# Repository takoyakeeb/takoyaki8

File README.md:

# takoyaki8

8キー(2行 × 4列)のマクロパッドです。マイコンは RP2040-Zero、ファームウェアは TinyGo(Go 言語)で書いています。
キーの割り当ては、Web ツール tinykeemap で書き換えられます。

## 特徴

- 8キー(2行 × 4列)。Choc v2 スイッチ(Choc v1 ではない)、ホットスワップ式(ソケット: CPG135001S30)
- マイコン: Waveshare RP2040-Zero
- 0.91 インチ OLED(128 × 32、I2C)と、フルカラー LED(WS2812B-V5)4個。OLED に、いまのレイヤーの番号と短い名前が出る
- ケース: トッププレート(メイン基板と同じパネルで製造)と、透明アクリル 2mm のボトムプレート・OLED カバー
- 4レイヤー。レイヤー切り替え(MO / TG / TO)と、Shift などの修飾キー付きのキーに対応
- キーマップは本体の Flash に保存できる(書き換えは tinykeemap)

## 部品リスト

### 基板に載せる部品

| 部品 | 型番・仕様 | 数量(1台) | 備考 |
|---|---|---|---|
| コンデンサ(C1〜C4) | 100nF、0603 | 4 | |
| ダイオード(D1〜D8) | 1N4148W、SOD-123(SMD) | 8 | COL2ROW(カソード側が Row 側) |
| フルカラー LED(LED1〜LED4) | WS2812B-V5(5050、PLCC4)。名前に「/W」が付かないもの | 4 | VIH 2.7V のものを選ぶ(3.3V の信号で動く) |
| 抵抗 0Ω(R1) | 0Ω、0603 | 1 | LED のデータ線の直列抵抗のパッド。0Ω で通す |
| 抵抗 330Ω または 470Ω(任意) | 0603 | 1 | LED がちらつくときに、R1 の代わりに入れる |
| マイコン(U1) | Waveshare RP2040-Zero(ハーフホールで基板に直接ハンダ付け) | 1 | ピンヘッダーなしの商品を選ぶ(付いていると、この取り付け方ができない) |
| OLED(J1) | 0.91 インチ、128×32、I2C、SSD1306 系。モジュールの基板に「Ver:1.6」の印字 | 1 | 外形寸法が違う型がある。同じ型を選ぶ |
| ピンヘッダー 1×4(J1 用) | 2.54mm ピッチ | 1 | OLED に付属のもの |

### スイッチ・キーキャップ・ケーブル

| 部品 | 型番・仕様 | 数量(1台) | 備考 |
|---|---|---|---|
| Choc v2 スイッチ | Kailh Choc v2(Choc v1 ではない)。サードパーティの Choc v2 でも使える | 8 | 軸の種類(リニア・タクタイル)は、お好みで |
| ホットスワップソケット | CPG135001S30(Kailh KH-PS-1702-35) | 8 | 基板に実装する |
| キーキャップ | Choc v2 対応で、幅が 19.05mm 以下のもの | 8 | |
| USB ケーブル | USB-C | 1 | データ通信ができるもの(充電専用は使えない) |

### ケース部品

| 部品 | 型番・仕様 | 数量(1台) | 備考 |
|---|---|---|---|
| スペーサー 5mm | 丸型・両メネジ、M2、外径 4.0mm、長さ 5mm | 4 | トッププレート用 |
| スペーサー 12mm | 丸型・両メネジ、M2、外径 4.0mm、長さ 12mm | 3 | カバー用 |
| ネジ M2×4 | M2 ナベ小ねじ(0番十字穴、頭径 2.9mm) | 14 | トッププレート用 8本、カバー用 6本 |
| カプトンテープ | — | 1 | OLED の裏に貼る |

### 基板とアクリル

| 部品 | 仕様 |
|---|---|
| メイン基板 + トッププレート | 1枚のパネル。99.9 × 82.1mm、2層、1.6mm、黄色、白シルク、無鉛 HASL |
| ボトムプレート + OLED カバー | 透明アクリル 2mm、彫刻あり |

## 基板・ケースの設計データ

設計データは `hardware/` にあります(KiCad 10.0。ライセンスは CERN-OHL-P-2.0)。ファイルの説明は、`hardware/README.md` を見てください。

Gerber と部品表(BOM)は、GitHub の[リリース](https://github.com/takoyakeeb/takoyaki8/releases)で配布しています。発注の手順と設定は、リリースの説明にあります。

## 組み立て

メイン基板、ケースの順に組み立てます。道具: はんだごて(温度調整つき)、細いはんだ、フラックス、ピンセット、テスター、拡大鏡、ヤスリ、ラジオペンチ、ニッパー。
0603 のチップ部品、SOD-123 のダイオード、5050 の LED など、小さな SMD 部品があります。

### メイン基板

低い部品から付けます。各段階のハンダ付けのあと、通電する前に、テスターで短絡を確認します。

1. **準備**: パネルからメイン基板を、手で折って切り離す。残った小さな突起は、ラジオペンチで取り、ヤスリで整える。トッププレートは、あとで使う。
2. **裏面(チップ部品)**: R1(0Ω)、C1〜C4(100nF)、D1〜D8、LED1〜LED4 の順に付ける。
   - ダイオードは、カソード(黒線側)を Row 側(基板のシルク▲マークの頂点側)にする(COL2ROW)。付けたあと、テスターのダイオードのモードで、順方向だけ導通する(目安 約0.5〜0.7V)ことを確認する。

   - LED は、1番ピン(欠けた角)とシルクの▲を合わせる。静電気に弱いので、触れる前に、身体の静電気を逃がす。
   - LED を付けたあと、VCC(5V)と GND が短絡していないことを確認する。
3. **裏面(ソケット)**: CPG135001S30 を8個付ける。位置決めの突起を穴に入れ、基板に密着させて、2か所の端子をパッドにハンダ付けする。
4. **表面(RP2040-Zero)**: 部品面を下にして、基板の窓に入れ、ハーフホールをハンダ付けする。USB-C は上辺側で、BOOT / RESET はボトムプレート側を向く。
   - 1か所を、マスキングテープなどで仮止めし、ハーフホールとパッドが全周で合っているか確認してから、すべてハンダ付けする。
   - 5V(VBUS)と GND、3V3 と GND が短絡していないことを確認する。
5. **表面(OLED)**: OLED 付属のピンヘッダーを、OLED 側に最低限の飛び出しでハンダ付けし、OLED の裏にカプトンテープを貼る。RP2040-Zero の上に乗せて、基板側をハンダ付けし、余ったピンをニッパーで切る。浮き量は約 2.95mm。OLED を傾けない。ガラスを強く押さない。
6. **動作の確認**: ファームを書き込み(次の「ファームウェアの書き込み」)、8キー(同時押しを含む)の入力と、LED、OLED の表示を確認する。そのあと、tinykeemap に接続して、キーマップを書き換えられることを確認する。
   - OLED は、USB-C を上にして置くと読める。「LAYER」の文字と、いまのレイヤーの大きな番号、短い名前が出る。

### ケース

基板の動作を確認してから組み立てます。寸法は、`hardware/case/README.md` にあります。下から上へ、重ねていきます。先に、ボトムプレートにスペーサーを付けます。

1. ボトムプレートの上に、スペーサーを立て、プレートの下から、M2×4 のネジで留める(5mm を4か所、12mm を3か所。ネジは計7本)。
2. トッププレートに、スイッチを2個はめる(四隅のうち、対角の2か所)。
3. 基板の穴にスペーサーを通して、ボトムプレートの上に、基板を重ねる。
4. トッププレートを、基板の上に重ね、2個のスイッチの端子を、基板のソケットに挿して、位置を決める。残りの6個のスイッチも、ソケットに挿す。トッププレートが基板側に落ちていたら、持ち上げる(すき間は約 0.5mm)。
5. トッププレートのネジ穴から、M2×4 のネジを通して、5mm のスペーサーに留める(4か所)。
6. OLED の上に、OLED カバー(アクリル)を置き、ネジ穴と 12mm のスペーサーを合わせて、M2×4 のネジで留める(3か所)。カバーの窓が、OLED の表示領域に合うことを確認する。
   - カバーは C1(右端が、基板の左端から 23.75mm)を使う。C2(24.5mm)は、幅 19mm のキーキャップに当たるので、使わない。
7. キーキャップを付けて、カバーに当たらないことを確認する。

ボトムプレートとカバーの彫刻面は、基板側(内側)に向けます。ボトムプレートには、USB 側の切り欠き(深さ 3.0mm)と、BOOT / RESET を押す穴(φ3.0)があります。組み立てたあとに、BOOT / RESET が押せること、USB ケーブルが挿せることを確認します。

3D プリントのバンパー(アクリルの外側を囲む枠)も使えます。ネジは使わず、上から落とし込みます。データは `hardware/case-3d/`、寸法と印刷の条件は、`hardware/README.md` の「バンパー(3D プリント)」にあります。

## ファームウェアの書き込み

書き込み方は2つです。TinyGo がなくても、ビルド済みの .uf2 で書き込めます。

### ビルド済みの .uf2 から書き込む

1. GitHub の[リリース](https://github.com/takoyakeeb/takoyaki8/releases)から、ファームのリリースの `.uf2` をダウンロードする。
2. RP2040-Zero の **BOOT ボタンを押しながら**、USB ケーブルで PC につなぐ(ケースに入れたあとは、ケースの穴から、ピンセットなどの先の細いもので押す)。
3. `RPI-RP2` という名前のドライブが現れる。
4. `.uf2` を、そのドライブに**コピー**する。コピーが終わると、自動で再起動する。
5. tinykeemap で接続して、キーボードが認識されることを確認する。

### ソースから書き込む

TinyGo が必要です。

1. このリポジトリを取得して、フォルダに移動する。

   ```bash
   git clone https://github.com/takoyakeeb/takoyaki8.git
   cd takoyaki8
   ```

2. RP2040-Zero の **BOOT ボタンを押しながら**、USB ケーブルで PC につなぐ。
3. ビルドと書き込みを行う。

   ```bash
   tinygo flash --target waveshare-rp2040-zero --size short .
   ```

.uf2 ファイルだけを作るときは、次のコマンドです。

```bash
tinygo build -target=waveshare-rp2040-zero -o takoyaki8.uf2 .
```

`main.go` の `debug` を `true` にすると、キーのイベントがシリアルに出ます。tinykeemap を使うときは、応答にデバッグの行が混ざるので、`false` のままにしてください。

### 初期キーマップ

レイヤー0 は MacOS の操作、レイヤー1 は編集とスクリーンショットです。OLED には、レイヤー0 は「MAC」、レイヤー1 は「EDIT」と出ます(名前は、ファームの中で固定)。キーごとの割り当ては、`model_takoyaki8.go` にもあります。

**レイヤー0(MAC)**

| | 1列目 | 2列目 | 3列目 | 4列目 |
|---|---|---|---|---|
| 上の行 | TO(1)(レイヤー1 へ) | ⌘ + Shift + Tab | ⌘ + Tab | Ctrl + ↓(ウィンドウ一覧) |
| 下の行 | F11 | Ctrl + ← | Ctrl + → | Ctrl + ↑(Mission Control) |

**レイヤー1(EDIT)**

| | 1列目 | 2列目 | 3列目 | 4列目 |
|---|---|---|---|---|
| 上の行 | TO(0)(レイヤー0 へ) | ⌘ + Shift + 3 | ⌘ + Shift + 4 | ⌘ + Shift + 5 |
| 下の行 | ⌘ + Z | ⌘ + X | ⌘ + C | ⌘ + V |

上の行の ⌘ + Shift + 3 / 4 / 5 は、スクリーンショットです。下の行は、元に戻す・切り取り・コピー・ペーストです。

保存済みのキーマップがある基板で、初期キーマップに戻すには、tinykeemap の RESET のあとに、SAVE も押します(RESET は、本体のメモリ(RAM)だけを初期値に戻すためです)。

## 設定ツール tinykeemap

キーマップは、Web ツール **tinykeemap** で書き換えます。インストールは不要で、キーボードを USB でつないで、ブラウザで開きます。

- 公開ページ: <https://takoyakeeb.github.io/tinykeemap/>
- 使い方・ソースコード: <https://github.com/takoyakeeb/tinykeemap>

できること: キーマップの表示・変更、Flash への保存(SAVE)、読み直し(LOAD)、初期キーマップへの復帰(RESET)。LED と OLED の設定は、まだできません。

対応ブラウザ(WebSerial が必要):

- おすすめ: PC 版の Chrome・Edge
- 未検証: Firefox 151 以降
- 使えない: Safari、スマートフォン

SAVE は、毎回、同じ1セクタ(Flash の最後の部分)に書き込みます。Flash の書き換え回数には限りがあり、一般的な目安は、1セクタあたり約10万回です。SAVE は、必要なときだけ押してください。

## 配線とピン配置

ピン配置と配線表は、[docs/wiring.md](docs/wiring.md) にあります(ピンの定義は `model_takoyaki8.go`)。

## ファイル構成

Go のファイルは、すべて `package main` で、リポジトリの直下にあります。

| ファイル | 役割 |
|---|---|
| `main.go` | 入口。起動時の準備と、メインループ(キーの読み取りと USB 送信、シリアルの処理、LED・OLED の更新) |
| `config.go` | 機種によらない設定(ファームのバージョン、行数・列数、LED・OLED の更新の間隔)。INFO の応答の元 |
| `model_takoyaki8.go` | 機種 takoyaki8 の値(機種名、ピン割り当て、レイヤー数、LED・OLED のピンと個数、初期キーマップ、レイヤー名の初期値) |
| `scanner.go` | 入力元の共通の形(キーイベントと、スキャナのインターフェース) |
| `matrix.go` | COL2ROW のマトリクススキャナ(チャタリングの除去を含む) |
| `keymap.go` | キーマップ(レイヤー × キー番号 = keycode) |
| `keycode.go` | keycode の定義(値は、tinykeemap の `docs/protocol.md` と同じ) |
| `layer.go` | レイヤー切り替えキー(MO / TG / TO)の処理 |
| `mods.go` | 修飾キーを押す・離す処理(複数のキーが同じ修飾キーを押していても、正しく離す) |
| `hid.go` | keycode を、TinyGo の USB キーボードの Keycode に変換 |
| `protocol.go` | tinykeemap との通信(INFO / GET / SET / DUMP / SAVE / LOAD / RESET)のコマンド処理 |
| `serial.go` | USB シリアルから1行ずつコマンドを受け取り、応答を返す |
| `flash.go` | キーマップの Flash への保存と読み込み(使える領域の最後の1セクタ。CRC32 で確認) |
| `led.go` | LED(WS2812B)の制御。確認用の動き(白い点が動く)で、tinykeemap からは設定できない |
| `oled.go` | OLED(SSD1306、128 × 32、I2C)の表示。レイヤーの番号と短い名前。名前は、ファームの中の固定の表で、tinykeemap からは設定できない |
| `go.mod`、`go.sum` | Go モジュールの定義と、依存ライブラリ(`tinygo.org/x/drivers`)の記録 |
| `docs/wiring.md` | 配線表とピン配置 |
| `docs/images/` | README の写真と、分解図 |
| `hardware/` | 基板(KiCad)とケース(アクリル)の設計データ(`hardware/README.md`) |
| `LICENSE` | ソフトウェアと文書のライセンス(MIT) |
| `LICENSE-HARDWARE` | 設計データのライセンス(CERN-OHL-P-2.0) |

## ライセンス

- ソフトウェア(ファームウェアの Go のファイル、`docs/` などの文書): MIT。全文は `LICENSE`。
- 基板・ケースの設計データ(`hardware/` と、ケースの図面): CERN-OHL-P-2.0(CERN Open Hardware Licence Version 2 - Permissive)。全文は `LICENSE-HARDWARE`。他人のファイル(Choc v2 のフットプリント)の出典は、`hardware/README.md`。
- tinykeemap は、別のリポジトリで、MIT。

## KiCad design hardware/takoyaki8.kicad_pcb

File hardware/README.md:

# hardware/ — takoyaki8 の設計データ

takoyaki8 の基板とケースの設計データです。

Copyright (c) 2026 takoyakeeb
SPDX-License-Identifier: CERN-OHL-P-2.0

## ライセンス

- この `hardware/` の中のファイル(ケースの図面を作るスクリプトを含む)は、下の「他人のファイル」を除いて、CERN-OHL-P-2.0(CERN Open Hardware Licence Version 2 - Permissive)です。全文は、リポジトリのルートの `LICENSE-HARDWARE` を見てください。
- ルートの `LICENSE`(MIT)は、ファームウェアと文書のライセンスです。

## 中身

| 場所 | 内容 |
|---|---|
| `takoyaki8.kicad_pro`、`takoyaki8.kicad_sch`、`takoyaki8.kicad_pcb` | KiCad のプロジェクト、回路図、基板。KiCad 10.0 で作成(古い版では、開けないことがあります) |
| `fp-lib-table`、`sym-lib-table` | ライブラリの表。自作ライブラリ(`lib/`)を指します |
| `lib/` | 自作のシンボル(RP2040-Zero)とフットプリント。出典と寸法は、`lib/README.md` |
| `case/` | ケース(アクリル)の寸法メモ(`README.md`)、図面を作るスクリプト(`acrylic_svg.py`、`export_formats.py`)とその検算(`check_acrylic_svg.py`。複数セット分の図面用)、配置データ(1台分は `layout_set1.json`、複数セット分は `layout_30x30_v2.json`)、1台分の図面(`drawings/`)、ロゴなどの素材(`art/`) |
| `case-3d/` | 3D プリントのケース(バンパー)。FreeCAD の元データ(`bumper.FCStd`)、`bumper.step`、`bumper.stl`。説明は、下の「バンパー」 |
| `gerber/` | KiCad から書き出した Gerber の置き場所(書き出しの設定は、プロジェクトに保存済み)。リポジトリには含めません(`.gitignore`)。配布は、GitHub のリリース `hw-rev1.0` |

## ケースの図面(アクリル)

1台分(ボトムプレート1枚と、OLED カバー C1 を1枚)の図面は、`case/drawings/` にあります。SVG・PDF・DXF の中身は同じで、大きさは 105.9 × 72.3mm です。

- SVG・PDF: 赤い線が切る線(1pt)、黒の塗りが彫刻です。
- DXF: 単位は mm。レイヤー `CUT` が切る線、`ENGRAVE` が彫刻の輪郭です。
- 彫刻は、基板側(内側)の面に入れるので、文字は鏡文字になっています。
- 材料の板の大きさには、合わせていません。複数セットを1枚に並べるときは、`layout_30x30_v2.json` を使います。
- 作り直す手順は、`case/acrylic_svg.py` の冒頭に書いてあります。

## 基板

- 2層、板厚 1.6mm。メイン基板とトッププレートを、1枚のパネルにしています。マウスバイトで切り離します。
- KiCad の DRC に、マウスバイトの穴の警告が24件出ます(意図した設計です)。
- 発注に使った版には、タグ `hw-rev1.0-order1` が付いています。

## バンパー(3D プリント)

アクリルのサンドイッチ(ボトムプレート、基板、トッププレート)の外側を囲む枠です。上から落とし込みます。ネジは使いません。

- 基板とアクリルは、斜めに挿し込んで入れます。下から指で押し上げて、外します。
- 底は塞がないので、BOOT/RESET の穴は、そのまま使えます。
- 壁の内側の小さな出っ張り(リブ)が、基板の側面を押さえるので、ひっくり返しても、中身は抜け落ちません。

### 寸法

単位は mm です。原点は、バンパーの中心です。上から見て、基板の上辺(USB 側)が +Y、基板の左端が -X です。高さ z は、バンパーの底の下面を 0 とします。

| 項目 | 値 |
|---|---|
| 外形 | 106.7 × 47.25(壁の厚み 3.0)。高さは、カバー側(x < -24.0)が 17.2、キー側(x > -24.0)が 12.7 |
| 内側の穴 | 100.7 × 41.25(基板 99.9 × 40.05 に対して、X は片側 0.4、Y は片側 0.6 のすき間) |
| 底の縁 | 厚み 1.0、内側へ 1.7(開口 97.3 × 37.85) |
| 角の丸め | 外側 R3.4、内側 R1.4。壁の高さの段差(x = -24.0)の角は、R1.5 |
| USB の開口 | +Y の壁に、幅 13.0(X -42.95 〜 -29.95)、底 2.2、天井 9.7(高さ 7.5)。上は壁でふさぐ。4つの角は、すべて R1.5。端子(基板の厚みを含めて、高さ 約4.5)の上下に、約 1.5 ずつ空く |
| USB の座ぐり | USB の開口のまわりを、外側から深さ 1.0 だけ浅く掘る(X -44.45 〜 -28.45、z 1.2 〜 10.7、角 R2.0)。ケーブルの根元が、深く入るようにするため |
| 押さえのリブ | +Y と -Y の壁に、向かい合わせで 4 組(8 個)。x = -46、-20、12、44。丸い出っ張りで、基板とトッププレートの側面に当たる |

リブの寸法(8 個とも、先の間隔は同じ):

- リブ先どうしの間隔 39.55(壁の内側からの突き出し 0.85。先端は Y = ±19.775)。基板の短辺(40.05。実測は 40.00〜40.02)に対して、設計の食い込みは、片側 0.23〜0.25
- 高さ z = 3.8 〜 10.2(底のアクリル(短辺 39.85。z = 1.0 〜 3.1)に当たらないよう、アクリルの上から始める)
- 幅は、x = -46(カバー側の端)が 4、ほかが 約 5
- 印刷すると、リブは、設計より片側 約0.08〜0.11 低く出る(実測のリブ先の間隔は 39.70〜39.76)。実際の食い込みは、片側 約0.12〜0.16

高さ: 底の縁の上面(z = 1.0)が、ボトムプレートの下面です。キー側の壁の上端(12.7)と、キーキャップの下端のすき間は、17mm のキーキャップで 1.5〜1.7、19mm のキーキャップで 約 0.2 です。

### 印刷の条件

- プリンター: Bambu Lab A1 mini(ノズル 0.4)、スライサー: Bambu Studio
- 材料: PLA(つや消しの白)
- 設定: 積層ピッチ 0.20、壁 4周(壁が 3.0 なので、壁の全体が外周の線で埋まるようにする)、サポートなし
- 向き: 底の縁を下にして、`bumper.stl` のまま置く。印刷時間は、約31分

### 印刷の注意

- 外形は、設計より約0.5%小さく出ます。すき間は、この縮みを見込んでいます。別のプリンターや材料では、縮み方が変わります。リブも、縮みの影響で、設計より低く出ます。
- 入れるときが固すぎるときは、リブの先を、細かい紙やすりで少し削ってください。ゆるいときは、リブ先の間隔を 0.1 ずつ小さくして、作り直してください(片側の食い込みが 0.05 ずつ増えます)。
- 温かいうちに剥がすと、底が反ります(0.4mm くらい)。プレートが完全に冷めてから、剥がしてください。

## 他人のファイル

- **Choc v2 のホットスワップソケットのフットプリント**(`lib/takoyaki8.pretty/SW_choc_v2_HS_CPG135001S30_1u.kicad_mod`): marbastlib の `marbastlib-xp-choc`(ebastler/marbastlib、CERN-OHL-P-2.0)から、2026-10-05 にコピーしました。寸法は、Kailh の資料と、実物で確認しています(`lib/README.md`)。3D モデル(STEP)は、パスで参照しているだけで、このリポジトリには含めていません。
- **KiCad 標準ライブラリの部品**(Capacitor_SMD、Diode_SMD、LED_SMD、Resistor_SMD): 回路図と基板に、部品として含まれています。KiCad のライブラリは CC-BY-SA 4.0 ですが、例外があり、ライブラリを設計に使うだけなら、設計データを CC-BY-SA にする必要はありません(<https://www.kicad.org/libraries/license/>)。ライブラリのファイルそのものは、このリポジトリに含めていません。
- RP2040-Zero のシンボルとフットプリントは、自作です。ピン配置は、Waveshare 公式の図を見て作りました(図そのものは含めていません)。
- ロゴ(`lib/takoyaki8.pretty/TakoyaKeeb_logo.kicad_mod`、`case/art/`)は、自作です。
- バンパー(`case-3d/`)は、自作です。他人のファイルは使っていません。

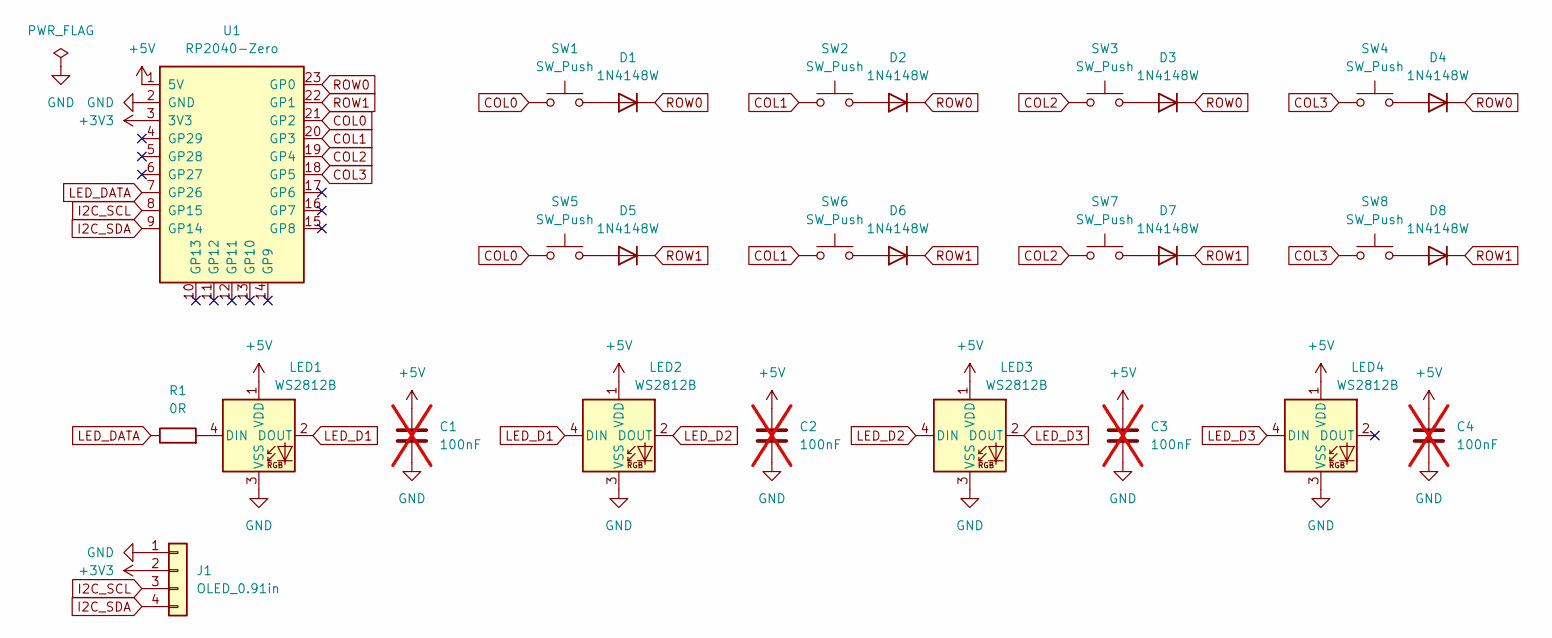
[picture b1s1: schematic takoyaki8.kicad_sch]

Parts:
C1, C2, C3, C4: 100nF; C_0603_1608Metric; not fitted
D1, D2, D3, D4, D5, D6, D7, D8: 1N4148W; D_SOD-123
J1: OLED_0.91in; OLED_0.91in_I2C_Header
LED1, LED2, LED3, LED4: WS2812B; LED_WS2812B_PLCC4_5.0x5.0mm_P3.2mm
R1: 0R; R_0603_1608Metric
SW1, SW2, SW3, SW4, SW5, SW6, SW7, SW8: SW_Push; SW_choc_v2_HS_CPG135001S30_1u
U1: RP2040-Zero; RP2040-Zero_Castellated_Flipped

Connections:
+3V3: J1.2, U1.3 (3V3)
+5V: C1.1, C2.1, C3.1, C4.1, LED1.1 (VDD), LED2.1 (VDD), LED3.1 (VDD), LED4.1 (VDD), U1.1 (5V)
COL0: SW1.1, SW5.1, U1.21 (GP2)
COL1: SW2.1, SW6.1, U1.20 (GP3)
COL2: SW3.1, SW7.1, U1.19 (GP4)
COL3: SW4.1, SW8.1, U1.18 (GP5)
GND: C1.2, C2.2, C3.2, C4.2, J1.1, LED1.3 (VSS), LED2.3 (VSS), LED3.3 (VSS), LED4.3 (VSS), U1.2 (GND)
I2C_SCL: J1.3, U1.8 (GP15)
I2C_SDA: J1.4, U1.9 (GP14)
LED_D1: LED1.2 (DOUT), LED2.4 (DIN)
LED_D2: LED2.2 (DOUT), LED3.4 (DIN)
LED_D3: LED3.2 (DOUT), LED4.4 (DIN)
LED_DATA: R1.1, U1.7 (GP26)
unnamed: D1.2 (A), SW1.2
unnamed: D2.2 (A), SW2.2
unnamed: D3.2 (A), SW3.2
unnamed: D4.2 (A), SW4.2
unnamed: D5.2 (A), SW5.2
unnamed: D6.2 (A), SW6.2
unnamed: D7.2 (A), SW7.2
unnamed: D8.2 (A), SW8.2
unnamed: LED1.4 (DIN), R1.2
ROW0: D1.1 (K), D2.1 (K), D3.1 (K), D4.1 (K), U1.23 (GP0)
ROW1: D5.1 (K), D6.1 (K), D7.1 (K), D8.1 (K), U1.22 (GP1)

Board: 2 copper layers, 33 parts (25 on the bottom side), 24 nets, no tracks yet.

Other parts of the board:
MB1, MB2, MB3, MB4, MB5, MB6: MouseBite; MouseBite_5x0.5mm_P0.85mm
